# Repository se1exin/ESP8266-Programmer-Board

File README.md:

# ESP8266 Programmer

Requires USB UART Breakout - https://www.sparkfun.com/products/13830

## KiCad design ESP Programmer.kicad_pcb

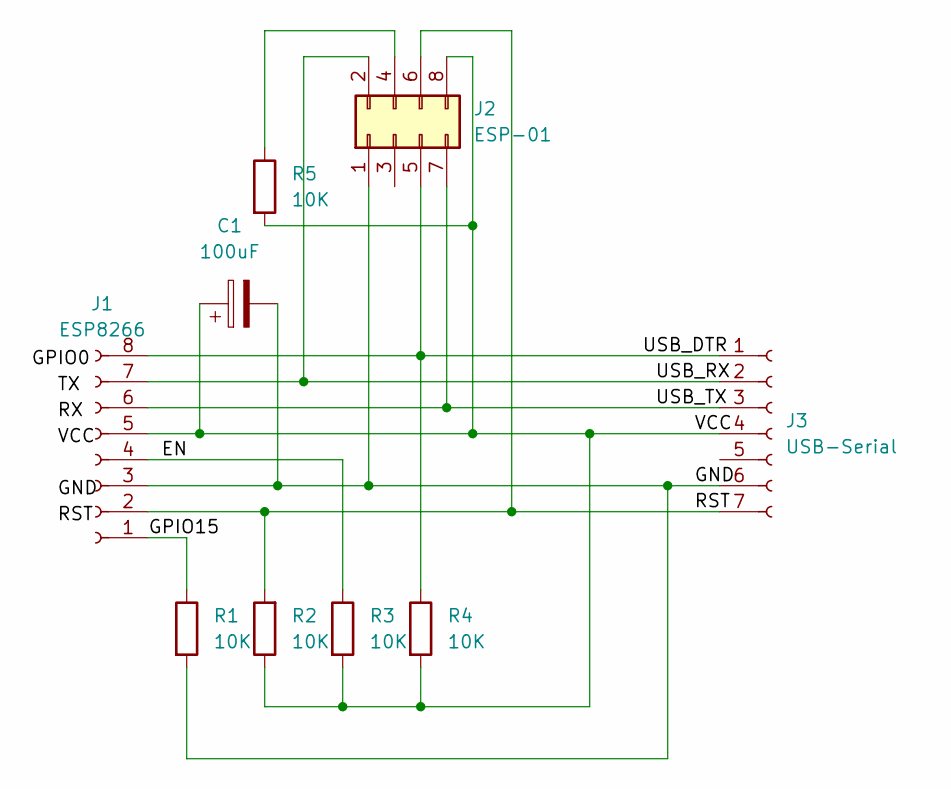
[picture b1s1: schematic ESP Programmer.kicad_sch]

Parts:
C1: 100uF; CP_Axial_L10.0mm_D4.5mm_P15.00mm_Horizontal
J1: ESP8266; PinHeader_1x08_P2.54mm_Vertical
J2: ESP-01; PinSocket_2x04_P2.54mm_Vertical
J3: USB-Serial; PinHeader_1x07_P2.54mm_Vertical
R1, R2, R3, R4, R5: 10K; R_Axial_DIN0411_L9.9mm_D3.6mm_P12.70mm_Horizontal

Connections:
/: J1.7, J2.2, J3.2
/EN: J1.4, R3.1
/GND: C1.2, J1.3, J2.1, J3.6, R1.2
/GPIO15: J1.1, R1.1
/RST: J1.2, J2.6, J3.7, R2.2
/USB_DTR: J1.8, J2.5, J3.1, R4.1
/USB_TX: J1.6, J2.7, J3.3
/VCC: C1.1, J1.5, J2.8, J3.4, R2.1, R3.2, R4.2, R5.2
unnamed: J2.4, R5.1

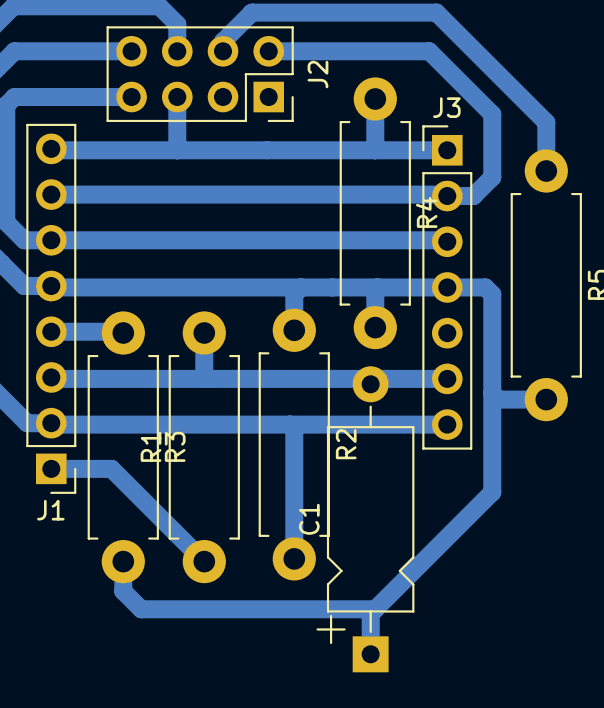
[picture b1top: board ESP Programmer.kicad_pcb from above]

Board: 2 copper layers, 9 parts (0 on the bottom side), 9 nets.
